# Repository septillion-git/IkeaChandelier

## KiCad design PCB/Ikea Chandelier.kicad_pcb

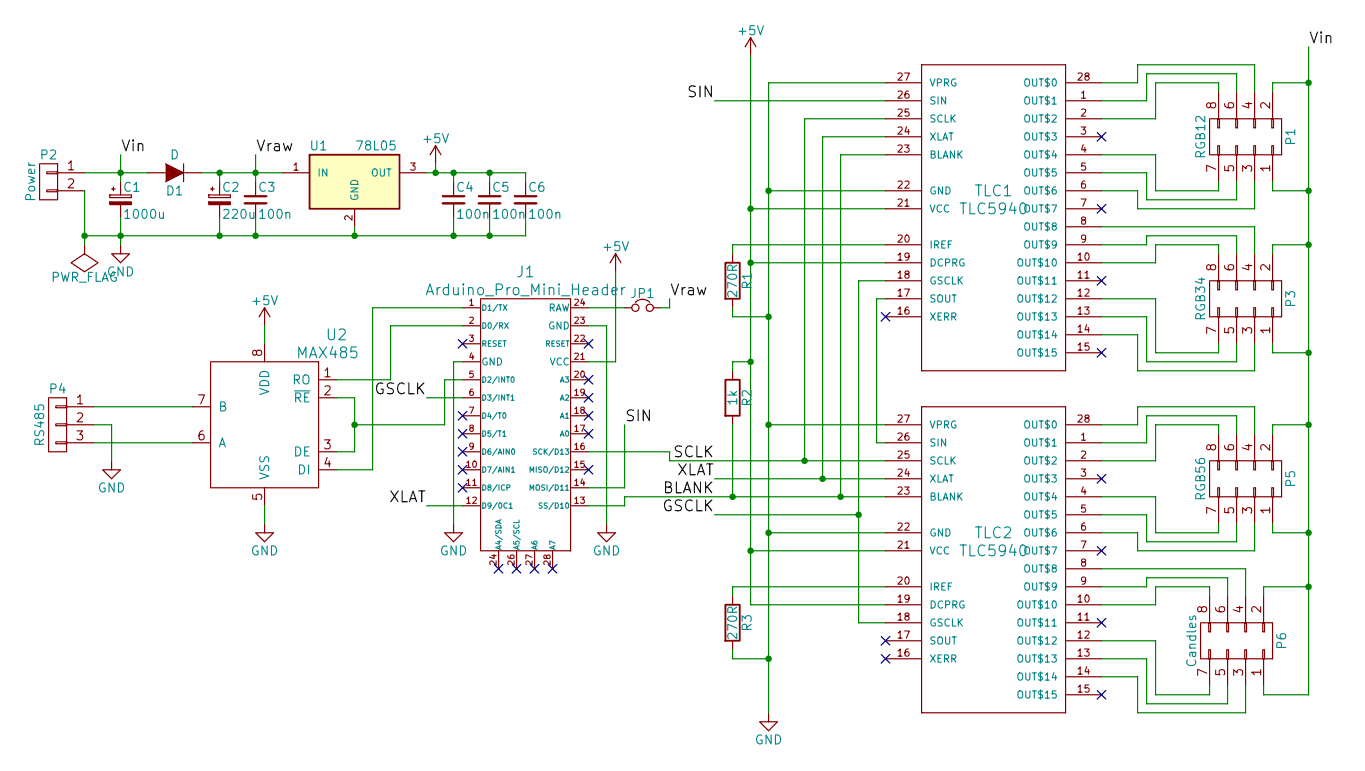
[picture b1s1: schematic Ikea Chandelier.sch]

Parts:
C1: 1000u; C_Radial_D5_L11_P2.5
C2: 220u; C_Radial_D5_L11_P2.5
C3, C4, C5, C6: 100n; C_0805
D1: D; D2
J1: Arduino_Pro_Mini_Header; arduino_pro_mini_(tail-less)_header
JP1: Jumper_NC_Small; SMD_jumper2
P1: RGB12; Pin_Header_Straight_2x04
P2: Power; bornier2
P3: RGB34; Pin_Header_Straight_2x04
P4: RS485; Pin_Header_Straight_1x03
P5: RGB56; Pin_Header_Straight_2x04
P6: Candles; Pin_Header_Straight_2x04
R1, R3: 270R; R_0805
R2: 1k; R_0805
TLC1, TLC2: TLC5940; DIP-28_W7.62mm_narrowPad
U1: 78L05; TO-92_Molded_Narrow
U2: MAX485; DIP-8_W7.62mm

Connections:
+5V: C4.1, C5.1, C6.1, J1.21 (VCC), R2.1, TLC1.19 (DCPRG), TLC1.21 (VCC), TLC2.19 (DCPRG), TLC2.21 (VCC), U1.3 (OUT), U2.8 (VDD)
/BLANK: J1.13 (SS/D10), R2.2, TLC1.23 (BLANK), TLC2.23 (BLANK)
/GSCLK: J1.6 (D3/INT1), TLC1.18 (GSCLK), TLC2.18 (GSCLK)
/SCLK: J1.16 (SCK/D13), TLC1.25 (SCLK), TLC2.25 (SCLK)
/SIN: J1.14 (MOSI/D11), TLC1.26 (SIN)
/Vin: C1.1, D1.2 (A), P1.1, P1.2, P2.1, P3.1, P3.2, P5.1, P5.2, P6.1, P6.2
/Vraw: C2.1, C3.1, D1.1 (K), JP1.2, U1.1 (IN)
/XLAT: J1.12 (D9/0C1), TLC1.24 (XLAT), TLC2.24 (XLAT)
GND: C1.2, C2.2, C3.2, C4.2, C5.2, C6.2, J1.4 (GND), J1.23 (GND), P2.2, P4.2, R1.2, R3.2, TLC1.22 (GND), TLC1.27 (VPRG), TLC2.22 (GND), TLC2.27 (VPRG), U1.2 (GND), U2.5 (VSS)
unnamed: J1.1 (D1/TX), U2.4 (DI)
unnamed: J1.2 (D0/RX), U2.1 (RO)
unnamed: J1.5 (D2/INT0), U2.2 (~RE), U2.3 (DE)
unnamed: J1.24 (A4/SDA), JP1.1
unnamed: P1.3, TLC1.6 (OUT$6)
unnamed: P1.4, TLC1.28 (OUT$0)
unnamed: P1.5, TLC1.5 (OUT$5)
unnamed: P1.6, TLC1.1 (OUT$1)
unnamed: P1.7, TLC1.4 (OUT$4)
unnamed: P1.8, TLC1.2 (OUT$2)
unnamed: P3.3, TLC1.14 (OUT$14)
unnamed: P3.4, TLC1.8 (OUT$8)
unnamed: P3.5, TLC1.13 (OUT$13)
unnamed: P3.6, TLC1.9 (OUT$9)
unnamed: P3.7, TLC1.12 (OUT$12)
unnamed: P3.8, TLC1.10 (OUT$10)
unnamed: P4.1, U2.7 (B)
unnamed: P4.3, U2.6 (A)
unnamed: P5.3, TLC2.6 (OUT$6)
unnamed: P5.4, TLC2.28 (OUT$0)
unnamed: P5.5, TLC2.5 (OUT$5)
unnamed: P5.6, TLC2.1 (OUT$1)
unnamed: P5.7, TLC2.4 (OUT$4)
unnamed: P5.8, TLC2.2 (OUT$2)
unnamed: P6.3, TLC2.14 (OUT$14)
unnamed: P6.4, TLC2.8 (OUT$8)
unnamed: P6.5, TLC2.13 (OUT$13)
unnamed: P6.6, TLC2.9 (OUT$9)
unnamed: P6.7, TLC2.12 (OUT$12)
unnamed: P6.8, TLC2.10 (OUT$10)
unnamed: R1.1, TLC1.20 (IREF)
unnamed: R3.1, TLC2.20 (IREF)
unnamed: TLC1.17 (SOUT), TLC2.26 (SIN)

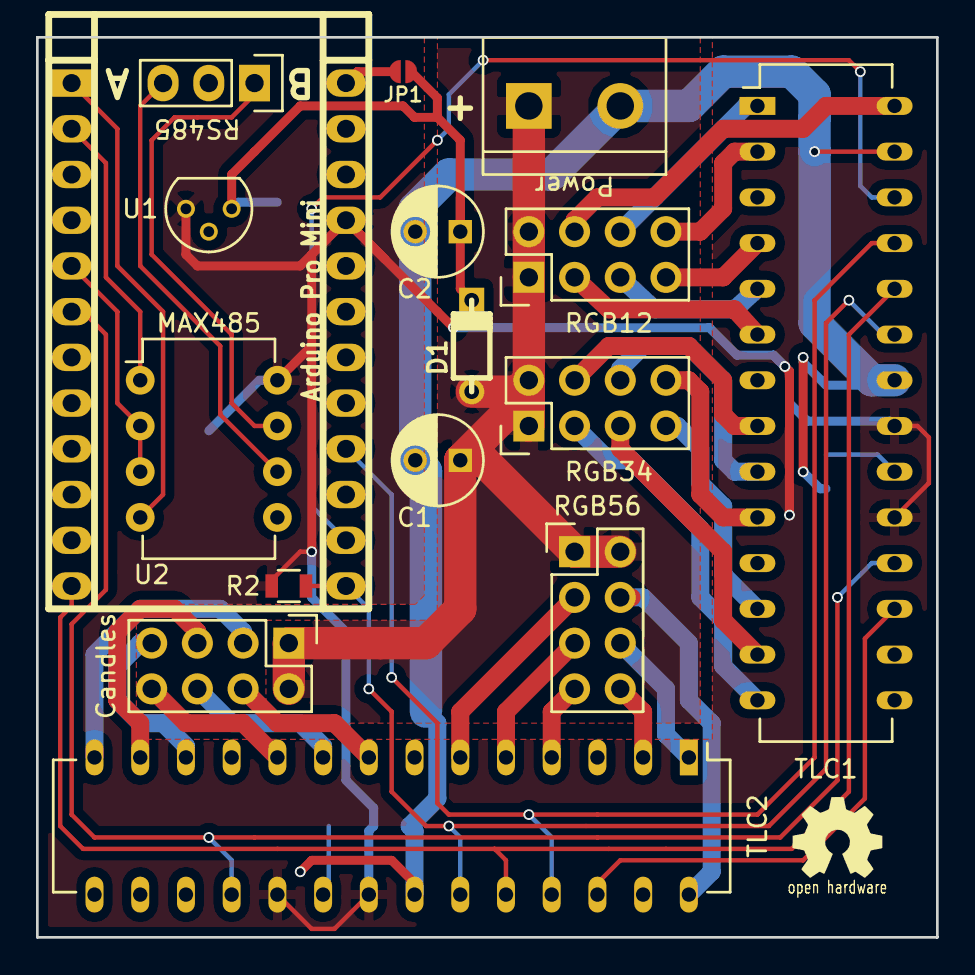
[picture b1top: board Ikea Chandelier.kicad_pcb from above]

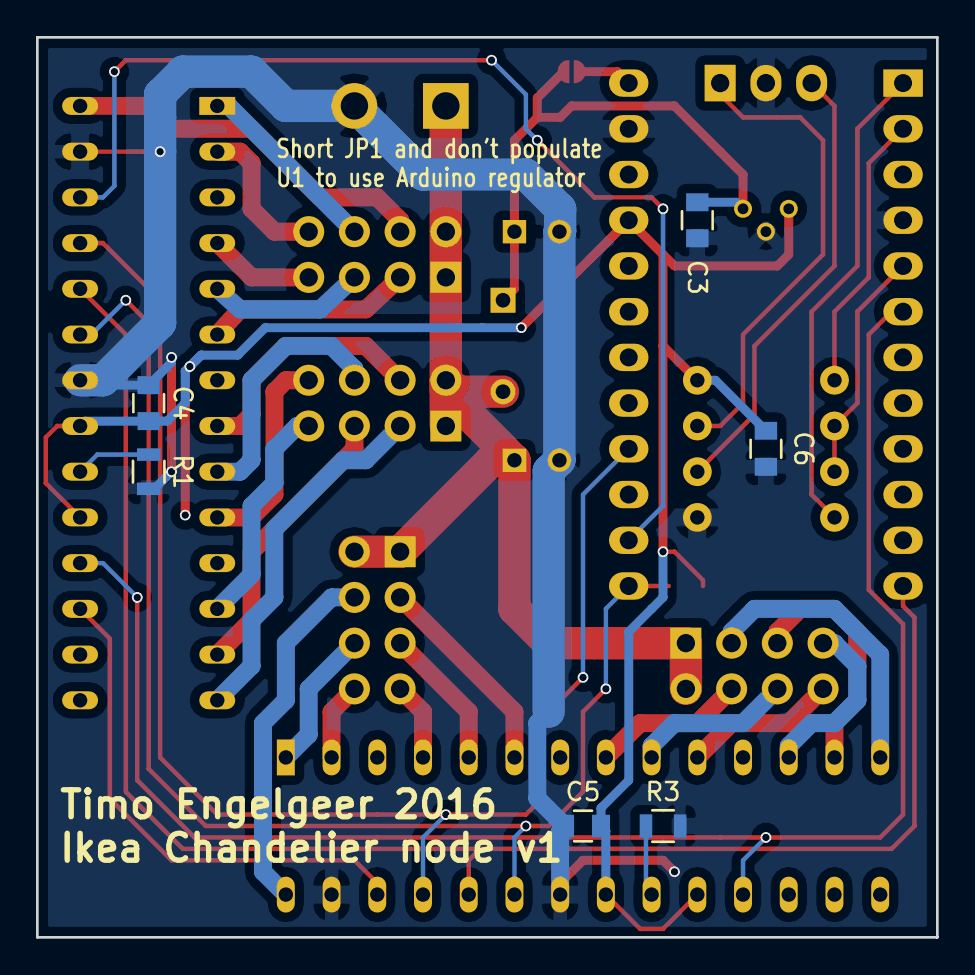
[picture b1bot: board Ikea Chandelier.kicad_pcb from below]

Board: 2 copper layers, 50.0 x 50.0 mm, 22 parts (6 on the bottom side), 42 nets.

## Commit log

2016-07-31 :boom::camel: Added .gitattributes & .gitignore files
2016-07-31 First project start
    Starting the project of making a Ikea (plastic cup) "Chandelier" +
    (livingroom) controller.
2016-08-04 SMD jumper + code testing
2016-08-05 Diode corrected, markings fixed, ordered v1
